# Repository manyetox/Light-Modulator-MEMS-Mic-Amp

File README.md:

<div align="center">

# Light Modulator + MEMS Mic Amp

**A compact two-board hardware platform for experimenting with optical audio modulation and MEMS microphone response.**

**Bluetooth audio → current-modulated LED/laser → MEMS microphone → audio amplifier**

</div>

> [!WARNING]
> **Laser safety:** This project can drive visible and near-infrared laser diodes. Near-IR beams may be difficult or impossible to see. Use the lowest practical optical power, a proper beam stop/enclosure, appropriate eye protection, and never aim a beam at people or reflective surfaces.

## Overview

This project is an experimental hardware platform for studying **optical audio injection into analogue microphones**.

It consists of two PCBs:

| Transmitter | Receiver |
|---|---|
| Receives audio over Bluetooth | Supports multiple analogue microphone types |
| Mixes stereo audio to mono | Low-noise microphone preamplifier |
| Adds adjustable DC bias and modulation depth | Speaker/audio output stage |
| Drives an LED or laser with an analogue current waveform | Allows microphone-to-microphone comparison |
| Uses a closed-loop current sink | Can be monitored with an oscilloscope |

The transmitter has already been **bench-tested and is functional**. Receiver validation is ongoing.

## Prototype

The first assembled transmitter and receiver prototypes are shown below.

### Prototype Demonstration

The animation below shows the assembled transmitter prototype operating and modulating the optical output from a Bluetooth audio source.

A longer demonstration of the prototype is also available:

▶ **[Watch the full prototype demonstration](Media/prototype-demo.mp4)**

## System Architecture

```mermaid
flowchart LR
    A[Phone / Audio Source] -->|Bluetooth| B[MH-M18]
    B --> C[Stereo-to-Mono Mix]
    C --> D[Modulation Depth]
    E[DC Bias] --> F[VSET]
    D --> F
    F --> G[CA3140 Control Loop]
    G --> H[IRLB8748 Current Sink]
    H --> I[LED / Laser]

    I -. Modulated Light .-> J[Analogue MEMS Microphone]
    J --> K[MCP6281 Preamp]
    K --> L[Volume Control]
    L --> M[LM386 Audio Amp]
    M --> N[Speaker / Oscilloscope]
```

## Transmitter

The transmitter converts Bluetooth audio into a controlled LED or laser current.

```text
Phone
  ↓ Bluetooth
MH-M18
  ↓
L/R audio mixed to mono
  ↓
Modulation-depth control
  ↓
DC bias + audio = VSET
  ↓
CA3140
  ↓
IRLB8748 current sink
  ↓
LED / laser diode
```

The CA3140 compares the requested control voltage (`VSET`) with the voltage across the current-sense resistor and drives the IRLB8748 until they match.

The approximate optical-source current is:

$$
I_{LED} \approx \frac{V_{SET}}{R_{SENSE}}
$$

This causes the LED or laser brightness to follow the audio waveform while maintaining an adjustable DC operating point.

### Main Transmitter Components

| Component | Function |
|---|---|
| **MH-M18** | Bluetooth audio receiver |
| **CA3140** | Current-control error amplifier |
| **IRLB8748** | Power MOSFET / controlled current sink |
| **LM7805** | 5 V supply for Bluetooth module |
| **RV2** | DC bias / optical operating point |
| **RV3** | Audio modulation depth |
| **R<sub>SENSE</sub>** | Sets the current range |

<details>
<summary><strong>Current-limit examples</strong></summary>

With the present bias network, the maximum DC `VSET` is approximately **0.82 V**.

| R<sub>SENSE</sub> | Approx. maximum DC current |
|---:|---:|
| 120 Ω | 6.8 mA |
| 22 Ω | 37 mA |
| 16.2 Ω | 51 mA |
| 4.3 Ω | 190 mA |

The resistor must be selected for the specific LED or laser being tested.

Audio modulation can create instantaneous current peaks above the DC operating point.

</details>

## Receiver

The receiver is designed to make the microphone response easy to hear and measure.

```text
Analogue microphone
  ↓
AC coupling
  ↓
MCP6281 preamplifier
  ↓
Volume control
  ↓
LM386 audio amplifier
  ↓
8 Ω speaker / oscilloscope
```

### Microphone Options

The receiver platform is intended for comparison between different analogue microphone technologies, including:

- **Infineon IM68A130** analogue MEMS microphone
- **TDK InvenSense ICS-40300** analogue MEMS microphone
- **ADMP401 breakout module** as a reference microphone
- Conventional electret microphone for control measurements

The onboard MCP6281 stage provides approximately **×48 voltage gain** for low-level microphone signals.

The LM386 provides the final power amplification for an 8 Ω speaker.

> [!NOTE]
> The ADMP401 breakout includes its own amplification, so it should be evaluated separately before feeding it through the full onboard microphone gain stage.

## Quick Start

1. **Choose the optical source.** Start with an LED before moving to a laser diode.
2. **Set the current range.** Select `R_SENSE` for the required current before connecting the optical device.
3. **Power the transmitter.** Verify the supply rails before fitting the LED or laser.
4. **Connect Bluetooth audio.** Pair a phone with the MH-M18 and play a low-volume test signal.
5. **Set the DC bias.** Increase the optical operating point gradually.
6. **Add modulation.** Increase the modulation-depth control while observing the output on an oscilloscope if available.
7. **Test the receiver.** Aim the modulated light at the microphone and monitor the recovered signal through the speaker or oscilloscope.

## Project Goals

This project is intended as a practical experimental platform for:

- reproducing and exploring optical-to-electrical coupling in analogue MEMS microphones;
- comparing microphone responses across different devices and optical wavelengths;
- testing different modulation depths, bias currents and optical sources;
- providing an inexpensive alternative to laboratory-only modulation hardware;
- making the phenomenon easy to demonstrate and measure on the bench.

## Project Status

| Subsystem | Status |
|---|---|
| Bluetooth audio input | ✅ Bench tested |
| Audio mixing / modulation | ✅ Bench tested |
| CA3140 + IRLB8748 current control | ✅ Bench tested |
| LED modulation | ✅ Bench tested |
| Laser-diode operation | 🧪 Device-dependent testing |
| MEMS receiver PCB | 🧪 Prototype / validation |
| Multi-microphone comparison | 🔬 Planned testing |

## Background

This project is inspired by the research presented in:

**T. Sugawara, B. Cyr, S. Rampazzi, D. Genkin and K. Fu,  
“Light Commands: Laser-Based Audio Injection Attacks on Voice-Controllable Systems,”  
29th USENIX Security Symposium, 2020.**

- [USENIX paper and presentation](https://www.usenix.org/conference/usenixsecurity20/presentation/sugawara)
- [Light Commands project website](https://lightcommands.com/)

The original research demonstrated that amplitude-modulated light can induce electrical signals in MEMS microphones.

This repository is an **independent experimental hardware implementation** intended for controlled research and educational testing.

## Safety and Responsible Use

This repository is intended for **laboratory, educational and defensive research**.

Do not direct lasers at people, vehicles, cameras, public devices or equipment you do not own or have explicit permission to test.

Use appropriate laser controls for the wavelength and optical power being used.

Infrared laser sources deserve particular care because the beam may not be visible.

## Contributing

Suggestions, measurements, microphone comparisons and hardware improvements are welcome.

For substantial changes, please open an issue first so the proposed change can be discussed before a pull request is prepared.

Useful contributions include:

- measurements from additional analogue MEMS microphones;
- optical wavelength comparisons;
- PCB and layout improvements;
- current-control stability measurements;
- oscilloscope captures and frequency-response data;
- documentation corrections.

## License

Copyright © 2026 Taylan Arslan.

This project is available for **research, educational, academic, personal, and other non-commercial use** under the terms of the [`LICENSE.md`](LICENSE.md) file.

**Commercial use is not permitted under the public license.**

Commercial manufacture, integration into a commercial product or service, internal commercial R&D, resale, or other commercial exploitation requires a **separate commercial license from the author**.

Commercial licenses may be provided for a fee. For commercial licensing enquiries, please contact **Taylan Arslan**.

The project is provided **as-is, without warranty**. Users are responsible for verifying the design, selecting appropriate components, complying with applicable regulations, and following electrical and laser-safety requirements.

See [`LICENSE.md`](LICENSE.md) for the complete terms.
## Author

**Taylan Arslan**

GitHub: [@manyetox](https://github.com/manyetox)

---

<div align="center">

### Light in. Audio out.

If this project helps your research, consider starring the repository.

</div>

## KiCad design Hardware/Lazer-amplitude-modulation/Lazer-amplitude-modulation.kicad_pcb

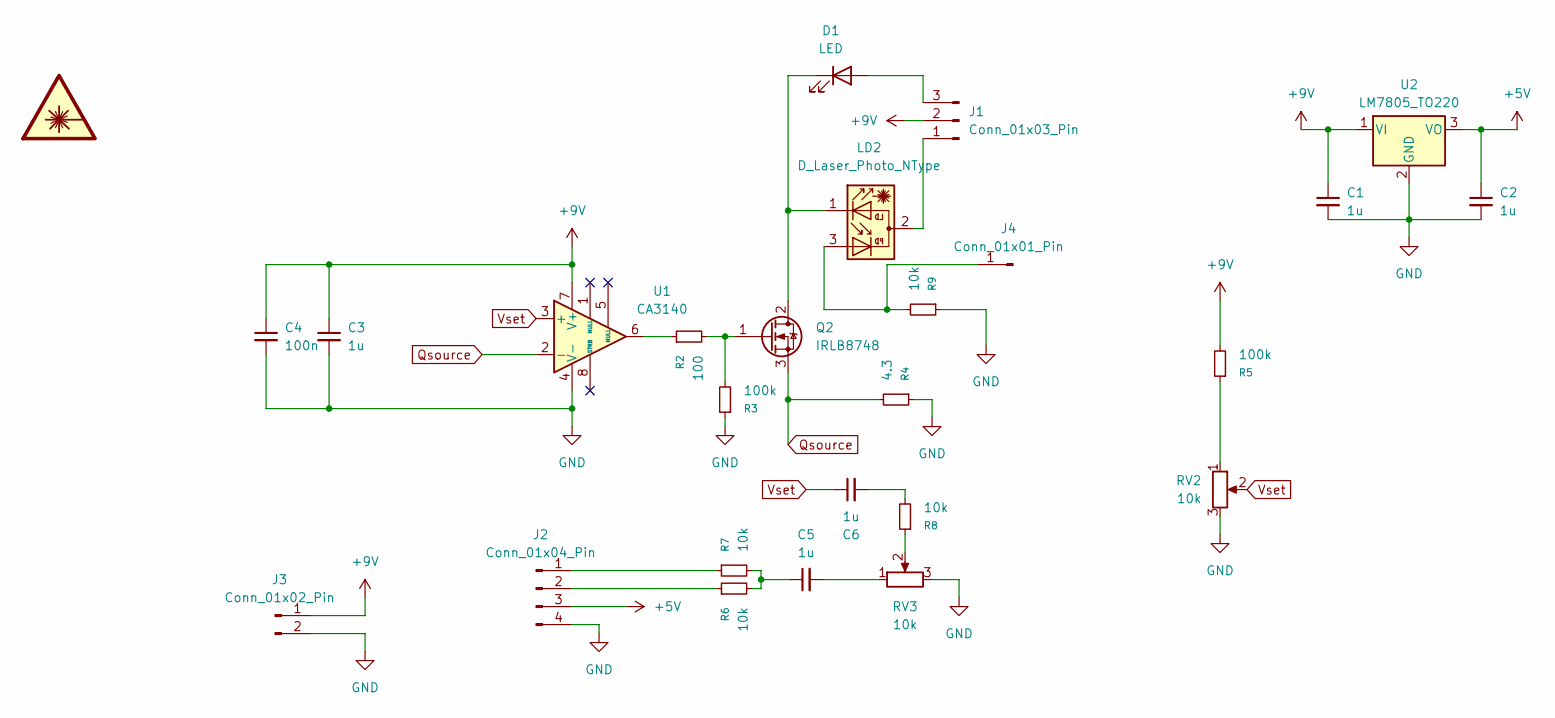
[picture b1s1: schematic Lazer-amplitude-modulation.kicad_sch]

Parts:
C1, C2, C3, C5, C6: 1u; C_0805_2012Metric_Pad1.18x1.45mm_HandSolder
C4: 100n; C_0805_2012Metric_Pad1.18x1.45mm_HandSolder
D1: LED; LED_D5.0mm
J1: Conn_01x03_Pin; PinHeader_1x03_P2.54mm_Vertical
J2: Conn_01x04_Pin; PinHeader_1x04_P2.54mm_Vertical
J3: Conn_01x02_Pin; PinHeader_1x02_P2.54mm_Vertical
J4: Conn_01x01_Pin; SolderWirePad_1x01_SMD_2x4mm
LD2: D_Laser_Photo_NType; LaserDiode_TO56-3
Q2: IRLB8748; TO-220-3_Vertical
R2: 100; R_0805_2012Metric_Pad1.20x1.40mm_HandSolder
R3, R5: 100k; R_0805_2012Metric_Pad1.20x1.40mm_HandSolder
R4: 4.3; R_0805_2012Metric_Pad1.20x1.40mm_HandSolder
R6, R7, R8, R9: 10k; R_0805_2012Metric_Pad1.20x1.40mm_HandSolder
RV2, RV3: 10k; Potentiometer_Bourns_3386F_Vertical
U1: CA3140; DIP-8_W7.62mm
U2: LM7805_TO220; TO-220-3_Vertical

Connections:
+5V: C2.1, J2.3, U2.3 (VO)
+9V: C1.1, C3.1, C4.1, J1.2, J3.1, R5.2, U1.7 (V+), U2.1 (VI)
GND: C1.2, C2.2, C3.2, C4.2, J2.4, J3.2, R3.1, R4.1, R9.1, RV2.3, RV3.3, U1.4 (V-), U2.2 (GND)
unnamed: C5.1, R6.2, R7.2
unnamed: C5.2, RV3.1
unnamed: C6.2, R8.2
unnamed: D1.2 (A), J1.3
unnamed: D1.1 (K), LD2.1, Q2.2 (D)
unnamed: J1.1, LD2.2
unnamed: J2.1, R7.1
unnamed: J2.2, R6.1
unnamed: J4.1 (Pin_1_1), LD2.3, R9.2
unnamed: Q2.1 (G), R2.2, R3.2
unnamed: R2.1, U1.6
unnamed: R5.1, RV2.1
unnamed: R8.1, RV3.2
Qsource: Q2.3 (S), R4.2, U1.2 (-)
Vset: C6.1, RV2.2, U1.3 (+)

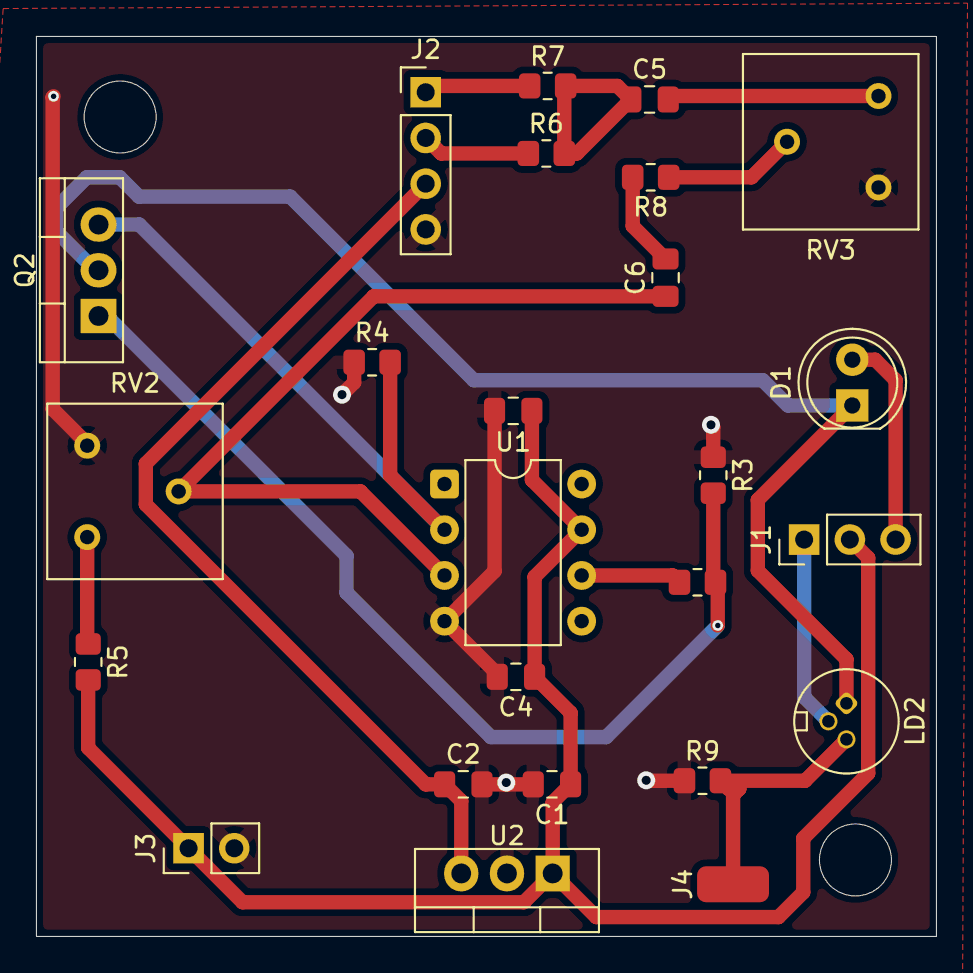
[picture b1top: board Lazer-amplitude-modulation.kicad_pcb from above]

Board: 2 copper layers, 50.0 x 50.0 mm, 25 parts (0 on the bottom side), 18 nets.

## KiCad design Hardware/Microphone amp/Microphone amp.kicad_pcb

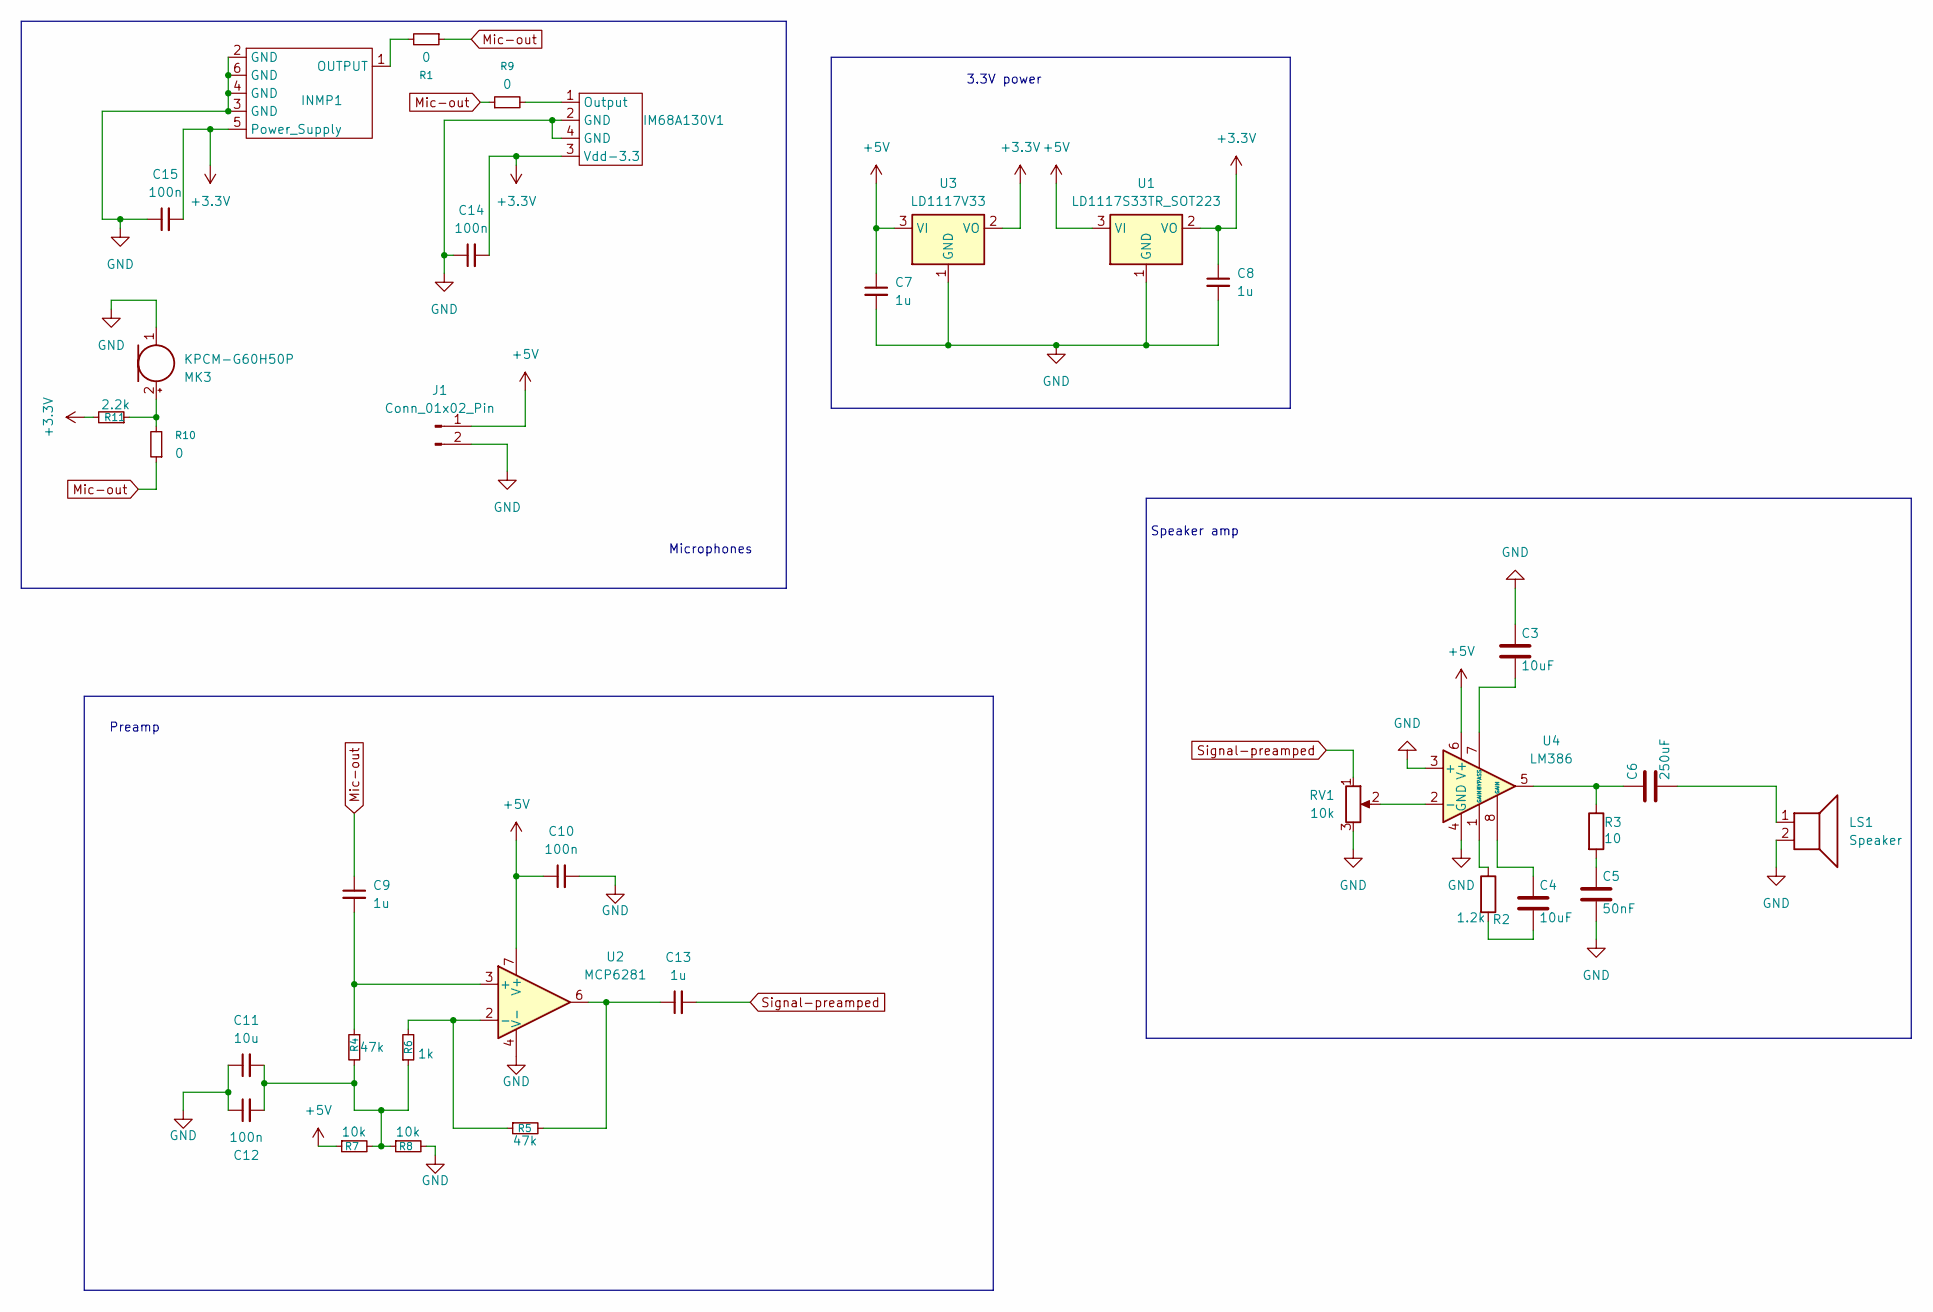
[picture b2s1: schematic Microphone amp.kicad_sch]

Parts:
C3, C4: 10uF; C_0805_2012Metric_Pad1.18x1.45mm_HandSolder
C5: 50nF; C_0805_2012Metric_Pad1.18x1.45mm_HandSolder
C6: 250uF; C_Radial_D6.3mm_H7.0mm_P2.50mm
C7, C8, C9, C13: 1u; C_0805_2012Metric_Pad1.18x1.45mm_HandSolder
C10, C12, C14, C15: 100n; C_0805_2012Metric_Pad1.18x1.45mm_HandSolder
C11: 10u; C_0805_2012Metric_Pad1.18x1.45mm_HandSolder
IM68A130V1: IM68A130V01
INMP1: INMP411
J1: Conn_01x02_Pin; PinHeader_1x02_P2.54mm_Vertical
LS1: Speaker; PinHeader_1x02_P2.54mm_Vertical
MK3: KPCM-G60H50P; CP_Radial_D5.0mm_P2.00mm
R1, R9, R10: 0; R_0402_1005Metric
R2: 1.2k; R_0805_2012Metric_Pad1.20x1.40mm_HandSolder
R3: 10; R_0805_2012Metric_Pad1.20x1.40mm_HandSolder
R4, R5: 47k; R_0805_2012Metric_Pad1.20x1.40mm_HandSolder
R6: 1k; R_0805_2012Metric_Pad1.20x1.40mm_HandSolder
R7, R8: 10k; R_0805_2012Metric_Pad1.20x1.40mm_HandSolder
R11: 2.2k; R_0805_2012Metric_Pad1.20x1.40mm_HandSolder
RV1: 10k; Potentiometer_Bourns_3386F_Vertical
U1: LD1117S33TR_SOT223; SOT-223-3_TabPin2
U2: MCP6281; DIP-8_W7.62mm
U3: LD1117V33; TO-220-3_Vertical
U4: LM386; DIP-8_W7.62mm_LongPads

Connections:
+3.3V: C8.1, C14.2, C15.2, IM68A130V1.3 (Vdd-3.3), INMP1.5 (Power_Supply), R11.2, U1.2 (VO), U3.2 (VO)
+5V: C7.1, C10.1, J1.1, R7.1, U1.3 (VI), U2.7 (V+), U3.3 (VI), U4.6 (V+)
GND: C3.1, C5.2, C7.2, C8.2, C10.2, C11.1, C12.1, C14.1, C15.1, IM68A130V1.2 (GND), IM68A130V1.4 (GND), INMP1.2 (GND), INMP1.3 (GND), INMP1.4 (GND), INMP1.6 (GND), J1.2, LS1.2, MK3.1 (-), R8.2, RV1.3, U1.1 (GND), U2.4 (V-), U3.1 (GND), U4.3 (+), U4.4 (GND)
Mic-out: C9.1, R1.1, R9.1, R10.1
unnamed: C4.1, U4.8 (GAIN)
unnamed: C4.2, R2.2
unnamed: C5.1, R3.2
unnamed: C6.1, R3.1, U4.5
unnamed: C6.2, LS1.1
unnamed: C11.2, C12.2, R4.2, R6.1, R7.2, R8.1
unnamed: C13.1, R5.2, U2.6
unnamed: IM68A130V1.1 (Output), R9.2
unnamed: INMP1.1 (OUTPUT), R1.2
unnamed: MK3.2 (+), R10.2, R11.1
unnamed: R2.1, U4.1 (GAIN)
unnamed: C9.2, R4.1, U2.3 (+)
unnamed: R5.1, R6.2, U2.2 (-)
unnamed: RV1.2, U4.2 (-)
unnamed: C3.2, U4.7 (BYPASS)
Signal-preamped: C13.2, RV1.1

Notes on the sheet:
Preamp
Microphones
Speaker amp
3.3V power

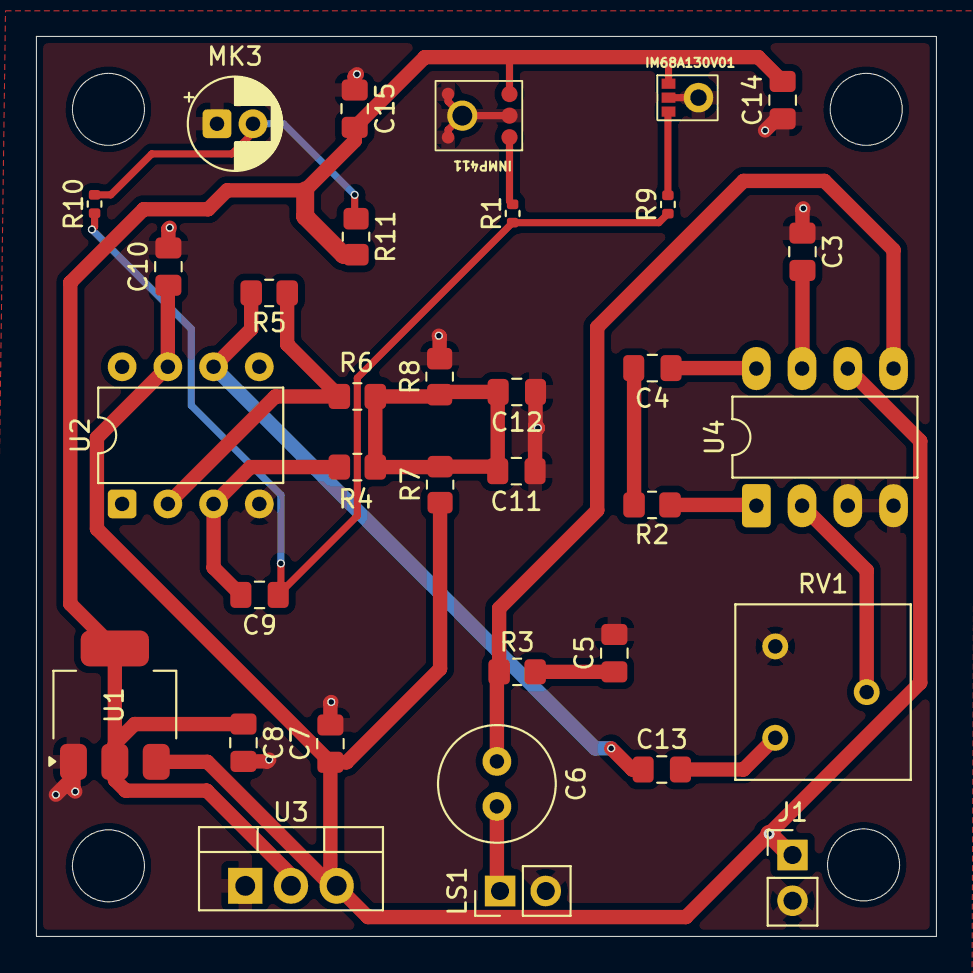
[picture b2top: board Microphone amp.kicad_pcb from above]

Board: 2 copper layers, 50.0 x 50.0 mm, 34 parts (0 on the bottom side), 20 nets.
